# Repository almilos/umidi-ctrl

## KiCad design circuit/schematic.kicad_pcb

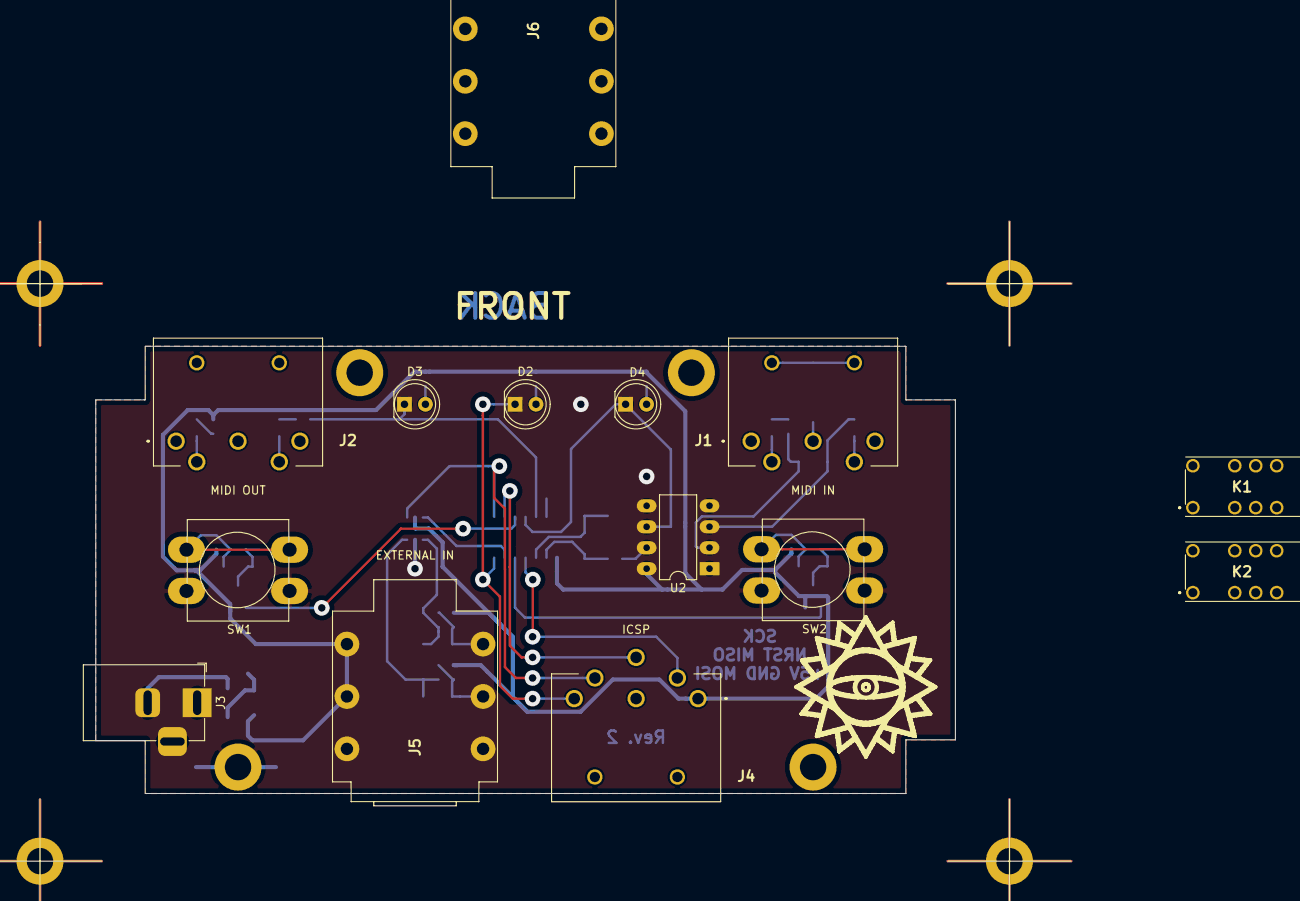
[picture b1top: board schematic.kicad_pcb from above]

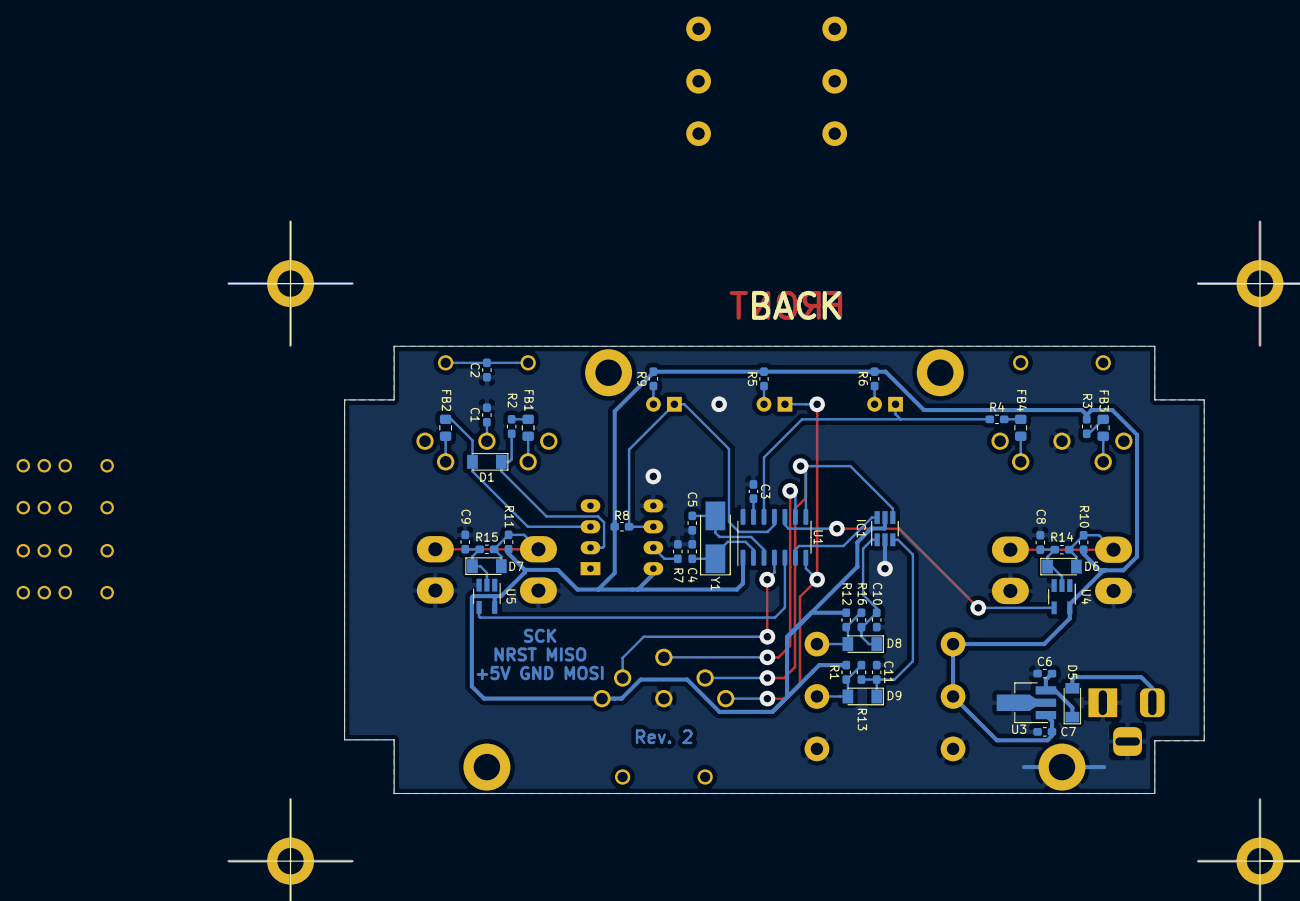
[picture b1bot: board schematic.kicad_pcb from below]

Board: 2 copper layers, 104.2 x 54.2 mm, 57 parts (43 on the bottom side), 38 nets.

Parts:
C1, C2, C7: 0.1u; C_0603_1608Metric_Pad1.05x0.95mm_HandSolder
C3: 0.1u; C_0603_1608Metric_Pad1.08x0.95mm_HandSolder
C4, C5: 22p; C_0603_1608Metric_Pad1.05x0.95mm_HandSolder
C6: 0.47u; C_0603_1608Metric_Pad1.05x0.95mm_HandSolder
C8, C9, C10, C11: 1u; C_0603_1608Metric_Pad1.05x0.95mm_HandSolder
D1, D5, D6, D7, D8, D9: LL4148; D_MiniMELF
D2, D3, D4: LED; LED_D5.0mm
FB1, FB2, FB3, FB4: Ferrite_Bead_Small; L_0805_2012Metric_Pad1.15x1.40mm_HandSolder
IC1: SN74LVC2G14DBVR; SOT-23-6_Handsoldering
J1, J2: DIN-5; KCDX5SN
J3: Barrel_Jack_Switch; BarrelJack_Horizontal
J4: DIN-6; KCDX6SN
J5, J6: AudioJack3_Dual_Switch; NYS2152
K1, K2: V23079A1001B301
R1, R10, R11, R12: 1k; R_0603_1608Metric_Pad1.05x0.95mm_HandSolder
R2, R3, R4: 220; R_0603_1608Metric_Pad1.05x0.95mm_HandSolder
R5: 270; R_0603_1608Metric_Pad1.05x0.95mm_HandSolder
R6, R9: 47; R_0603_1608Metric_Pad1.05x0.95mm_HandSolder
R7: 5.1k; R_0603_1608Metric_Pad1.05x0.95mm_HandSolder
R8: 1.2k; R_0603_1608Metric_Pad1.05x0.95mm_HandSolder
R13, R14, R15, R16: 20k; R_0603_1608Metric_Pad1.05x0.95mm_HandSolder
SW1, SW2: SW_Push; SW_PUSH-12mm
U1: ATtiny841-SSU; SOIC-14_3.9x8.7mm_P1.27mm
U2: 6N138; DIP-8_W7.62mm_LongPads
U3: L78L05_SOT89; SOT-89-3_Handsoldering
U4, U5: 74HC1G14GV,125; SOT-23-5_HandSoldering
Y1: 16M; Crystal_SMD_5032-2Pin_5.0x3.2mm_HandSoldering

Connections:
+5V: C7.2, IC1.5, J4.5, J5.RN, J5.TN, R1.2, R3.1, R5.2, R6.2, R8.2, R9.2, R10.2, R11.2, R12.2, U1.1, U2.8, U3.1, U4.5, U5.5
+9V: C6.2, D5.1, U3.3
BTN0: U1.10, U4.4
BTN1: U1.5, U5.4
BTN_EXT_R: IC1.4, J4.2, U1.8
BTN_EXT_T: IC1.6, U1.6
GND: C1.2, C2.2, C3.1, C4.1, C5.2, C6.1, C7.1, C8.1, C9.1, C10.1, C11.1, IC1.2, J2.3, J3.1, J3.3, J4.3, J5.S, J5.SN, R7.2, SW1.1, SW2.1, U1.14, U2.5, U3.2, U4.3, U5.3
MOSI: D2.1, J4.1, U1.7
NRST: J4.4, U1.4
unnamed: C1.1, J1.3
unnamed: C3.2, U1.13
unnamed: C4.2, U1.2, Y1.1
unnamed: C5.1, U1.3, Y1.2
unnamed: C8.2, D6.1, R14.2, U4.2
unnamed: C9.2, D7.1, R15.1, U5.2
unnamed: C10.2, D8.1, IC1.1, R16.1
unnamed: C11.2, D9.1, IC1.3, R13.1
unnamed: D1.1, R2.1, U2.2
unnamed: D1.2, FB2.2, U2.3
unnamed: D2.2, R5.1
unnamed: D3.2, R6.1
unnamed: D4.2, R9.1
unnamed: D5.2, J3.2
unnamed: D6.2, R10.1, R14.1, SW1.2
unnamed: D7.2, R11.1, R15.2, SW2.2
unnamed: D8.2, J5.T, R12.1, R16.2
unnamed: D9.2, J5.R, R1.1, R13.2
unnamed: FB1.1, R2.2
unnamed: FB1.2, J1.4
unnamed: FB2.1, J1.2
unnamed: FB3.1, J2.4
unnamed: FB3.2, R3.2
unnamed: FB4.1, J2.2
unnamed: FB4.2, R4.2
unnamed: R7.1, U2.7
RXD0: D4.1, R8.1, U1.11, U2.6
SCK: J4.6, U1.9
TXD0: D3.1, R4.1, U1.12

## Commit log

2021-05-19 Init commit
2021-05-25 Add board rev.2
